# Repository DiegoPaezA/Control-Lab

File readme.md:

# Low-cost control laboratory kit - Control(LAB)

<p align="justify">Control(Lab) is developed following the <a href="https://is.gd/1HAwDJ">TCLab</a> idea: a printed circuit board (PCB) that allows connection with the Arduino processing unit. The board has three transistors that work as heaters and three temperature sensors to follow the temperature variations in each heater. The operation of the plant is based on the control of the electrical current that flows through the transistors using the pulse width modulation (PWM) generated from the system's processing unit. The control action generates a variation in the temperature of the plant heaters limited by software to 100°C. This variation is measured by the temperature sensors and registered in the Arduino, thus establishing a closed control loop.</p>

<p align="justify">To develop an affordable and easy-to-build control lab kit, low-cost and easily accessible elements were selected. The LM35 temperature sensor replaced the TMP36 temperature sensor used in the TCLAB reference plant; the new sensor fulfills the necessary operating and functionality ranges. The sensor is linear and generates a voltage output proportional to the temperature variation (T° C = 10mV). Also, it has calibrated precision of 1°C, its measurement range is -55 ° C to 150 ° C, and it has a guaranteed precision of 0.5°C at 25°C ambient temperature. Finally, the configuration of three TIP31C NPN transistors (BJTs) as heaters allows implementing controllers of the single-input-single-output (SISO) type or multiple-input multiple-output (MIMO) with a low-cost and accessible device. Figure 1 shows the Control kit (Lab).</p>

<p align="justify">This repository presents different examples focused on testing the operation of the different ESP32 functionalities using FreeRTOS. The examples have been validated using an ESP32 DEVKIT DOIT board and the documentation of each of the examples is being done to address the theoretical concepts of each of the topics addressed.</p>

## References

Detailed description of the Control(Lab) can be find on the on the Article: [Comparative Study of PID, DMC, and Fuzzy PD+I Controllers in a Control Laboratory Kit](https://ieeexplore.ieee.org/document/9981589)

D. P. Ardila, D. M. Reyes, C. V. Niño, R. Tanscheit and M. Vellasco, "Comparative Study of PID, DMC, and Fuzzy PD+I Controllers in a Control Laboratory Kit," 2022 IEEE Latin American Conference on Computational Intelligence (LA-CCI), Montevideo, Uruguay, 2022, pp. 1-6, doi: 10.1109/LA-CCI54402.2022.9981589.

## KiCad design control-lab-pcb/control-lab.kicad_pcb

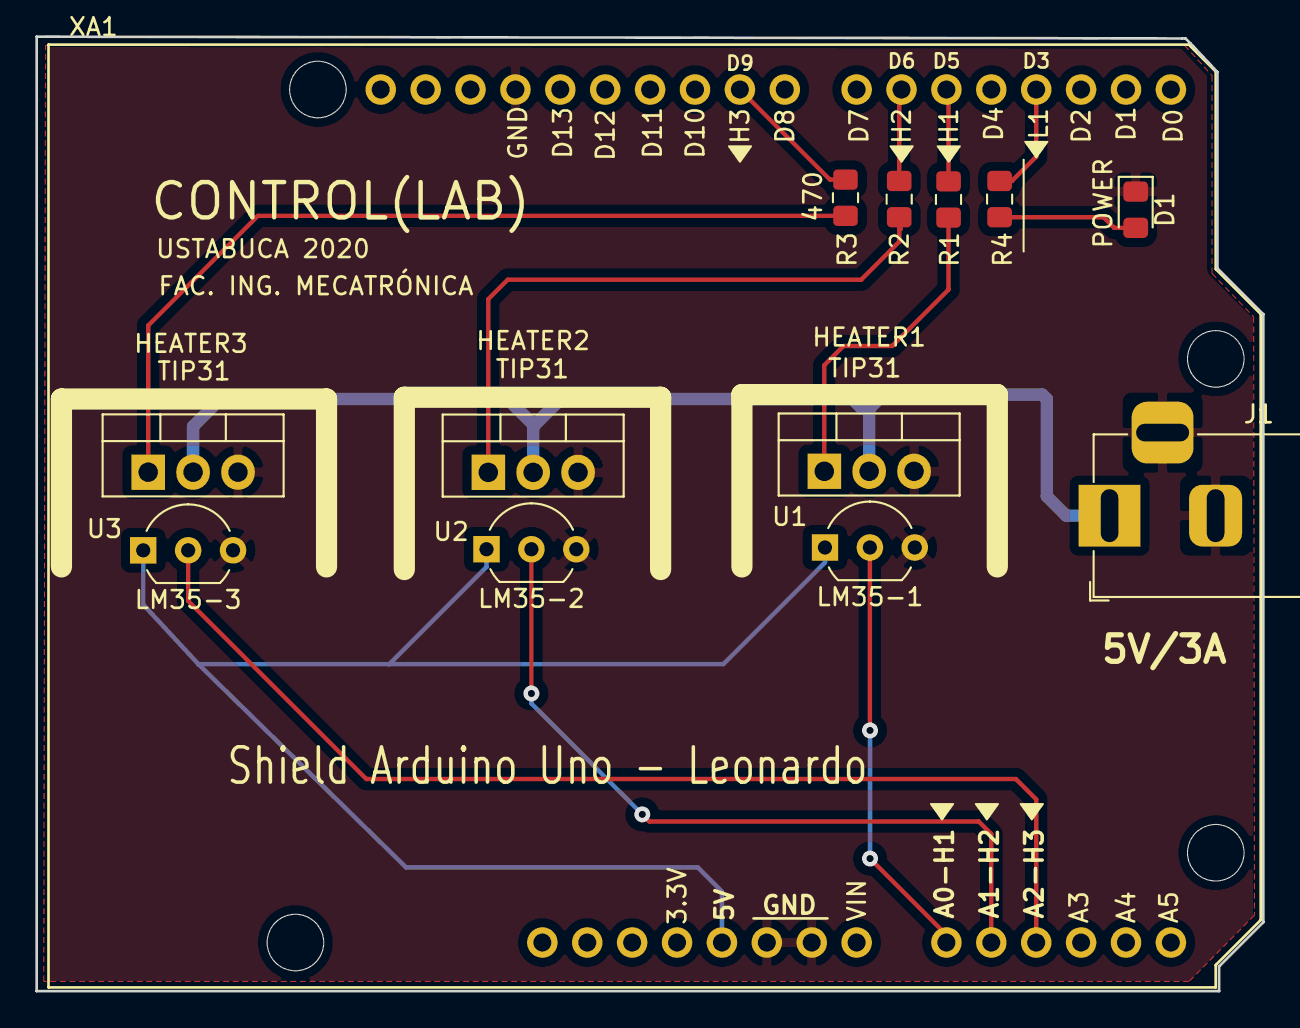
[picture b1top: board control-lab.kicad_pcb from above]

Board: 2 copper layers, 69.4 x 54.0 mm, 13 parts (0 on the bottom side), 14 nets.

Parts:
D1: POWER; LED_0805_2012Metric_Pad1.15x1.40mm_HandSolder
HEATER1, HEATER2, HEATER3: TIP31; TO-220-3_Vertical
J1: External Vin 5V; BarrelJack_Horizontal
R1, R2, R3, R4: 470; R_0805_2012Metric_Pad1.15x1.40mm_HandSolder
U1: LM35-1; TO-92_Inline_Wide
U2: LM35-2; TO-92_Inline_Wide
U3: LM35-3; TO-92_Inline_Wide
XA1: Arduino_Uno_Shield; Arduino_Leonardo_Shield

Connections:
+5V: U1.1, U2.1, U3.1, XA1.5V1
+VDC: HEATER1.2, HEATER2.2, HEATER3.2, J1.1
A0: U1.2, XA1.A0
A1: U2.2, XA1.A1
A2: U3.2, XA1.A2
GND: D1.1, HEATER1.3, HEATER2.3, HEATER3.3, J1.2, J1.3, U1.3, U2.3, U3.3, XA1.GND1, XA1.GND2, XA1.GND3
unnamed: D1.2, R4.1
unnamed: HEATER1.1, R1.1
unnamed: HEATER2.1, R2.1
unnamed: HEATER3.1, R3.1
PWM_3: R4.2, XA1.D3
PWM_5: R1.2, XA1.D5
PWM_6: R2.2, XA1.D6
PWM_9: R3.2, XA1.D9

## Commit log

2022-07-11 Control(Lab) Project
2022-07-11 link tclab update
2022-07-11 License
2022-08-03 Article Figures
2022-08-03 font size increased
2022-08-03 comments update
